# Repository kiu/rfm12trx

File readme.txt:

rfm12trx - A simple RFM12 433Mhz transceiver
http://schoar.de/tinkering/rfm12trx

1. Flash the RT232RL through USB
    http://www.ftdichip.com/Support/Utilities.htm#FT_Prog
    See firmware/rfm12trx_ftprog.xml (12Mhz on CBUS0)

2. Flash the ATMega8 through ISP
    make fuse
    make program

3. Send/Receive hex strings via ttyUSBx, e.g. screen /dev/ttyUSB0 115200

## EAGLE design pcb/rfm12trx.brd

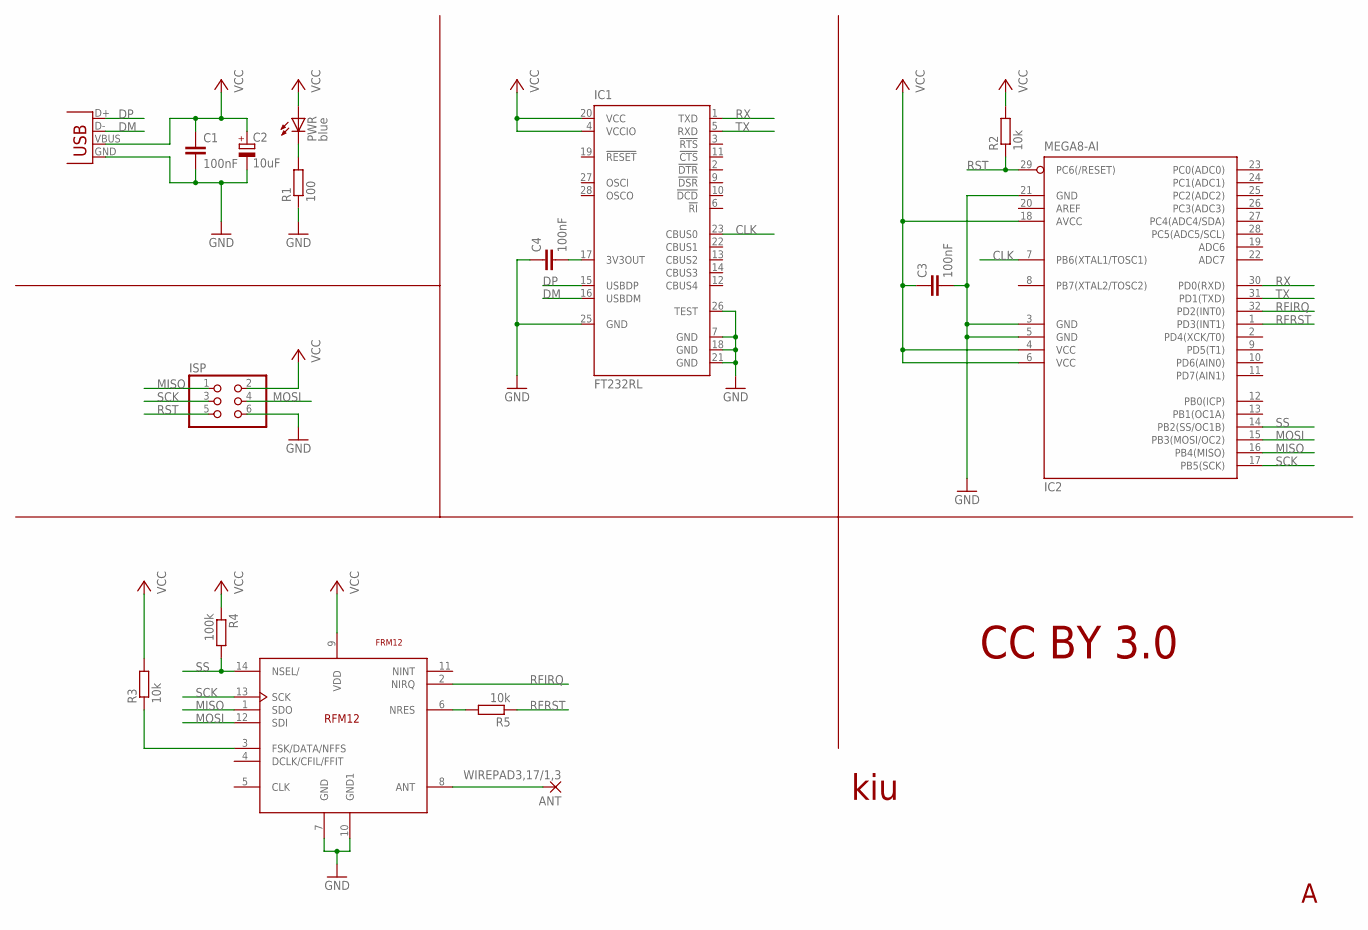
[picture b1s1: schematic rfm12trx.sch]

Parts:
ANT: WIREPAD3,17/1,3; 3,17/1,3
C1, C3, C4: 100nF; C0603
C2: 10uF; CT3216
IC1: FT232RL; SSOP28
IC2: MEGA8-AI; TQFP32-08
ISP: PINHD-2X3; 2X03
PWR: blue; CHIP-LED0805
R1: 100; R0603
R2, R3, R5: 10k; R0603
R4: 100k; R0603
U$1: FRM12; RFM12
X1: USB-MICROB

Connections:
CLK: IC1.23 (CBUS0), IC2.7 (PB6(XTAL1/TOSC1))
DM: IC1.16 (USBDM), X1.D-
DP: IC1.15 (USBDP), X1.D+
GND: C1.2, C2.-, C3.2, C4.1, IC1.7 (GND), IC1.18 (GND), IC1.21 (GND), IC1.25 (GND), IC1.26 (TEST), IC2.3 (GND), IC2.5 (GND), IC2.21 (GND), ISP.6, R1.1, U$1.7 (GND), U$1.10 (GND1), X1.GND
MISO: IC2.16 (PB4(MISO)), ISP.1, U$1.1 (SDO)
MOSI: IC2.15 (PB3(MOSI/OC2)), ISP.4, U$1.12 (SDI)
unnamed: PWR.C, R1.2
unnamed: C4.2, IC1.17 (3V3OUT)
unnamed: R3.1, U$1.3 (FSK/DATA/NFFS)
unnamed: R5.2, U$1.6 (NRES)
unnamed: ANT.1, U$1.8 (ANT)
RFIRQ: IC2.32 (PD2(INT0)), U$1.2 (NIRQ)
RFRST: IC2.1 (PD3(INT1)), R5.1
RST: IC2.29 (PC6(/RESET)), ISP.5, R2.1
RX: IC1.1 (TXD), IC2.30 (PD0(RXD))
SCK: IC2.17 (PB5(SCK)), ISP.3, U$1.13 (SCK)
SS: IC2.14 (PB2(SS/OC1B)), R4.2, U$1.14 (NSEL/)
TX: IC1.5 (RXD), IC2.31 (PD1(TXD))
VCC: C1.1, C2.+, C3.1, IC1.4 (VCCIO), IC1.20 (VCC), IC2.4 (VCC), IC2.6 (VCC), IC2.18 (AVCC), ISP.2, PWR.A, R2.2, R3.2, R4.1, U$1.9 (VDD), X1.VBUS

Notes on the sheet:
CC BY 3.0
kiu

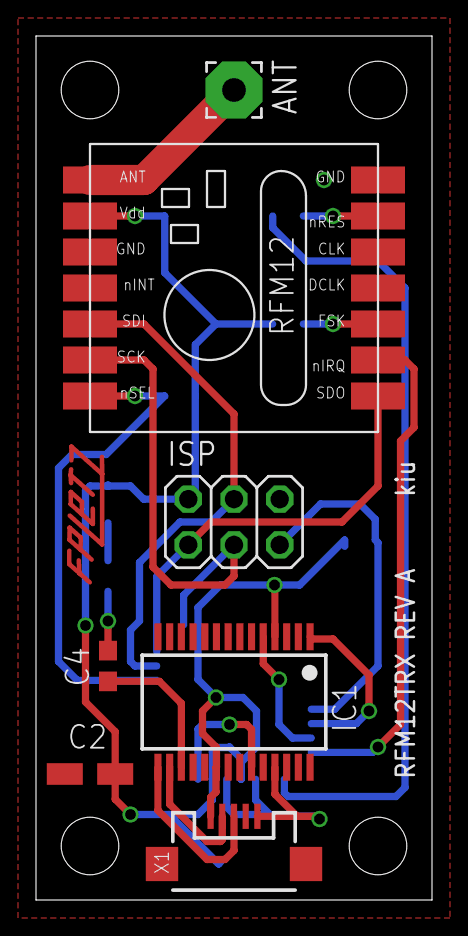
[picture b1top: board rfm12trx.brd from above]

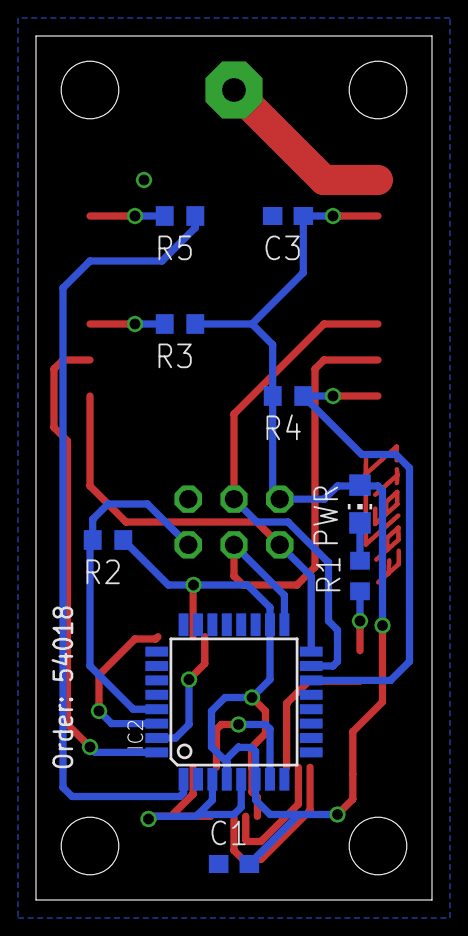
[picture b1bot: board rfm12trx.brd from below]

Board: 2 copper layers, 22.0 x 48.0 mm, 16 parts (9 on the bottom side), 19 nets.

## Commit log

2012-08-09 init
2012-08-18 Adding BOM
2012-08-18 Adding mechnical files
2012-08-19 typo
2012-08-19 adding pics

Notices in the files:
parts and their libraries:
SparkFun: Licensing: CC v3.0 Share-Alike You are welcome to use this library for commercial purposes.
